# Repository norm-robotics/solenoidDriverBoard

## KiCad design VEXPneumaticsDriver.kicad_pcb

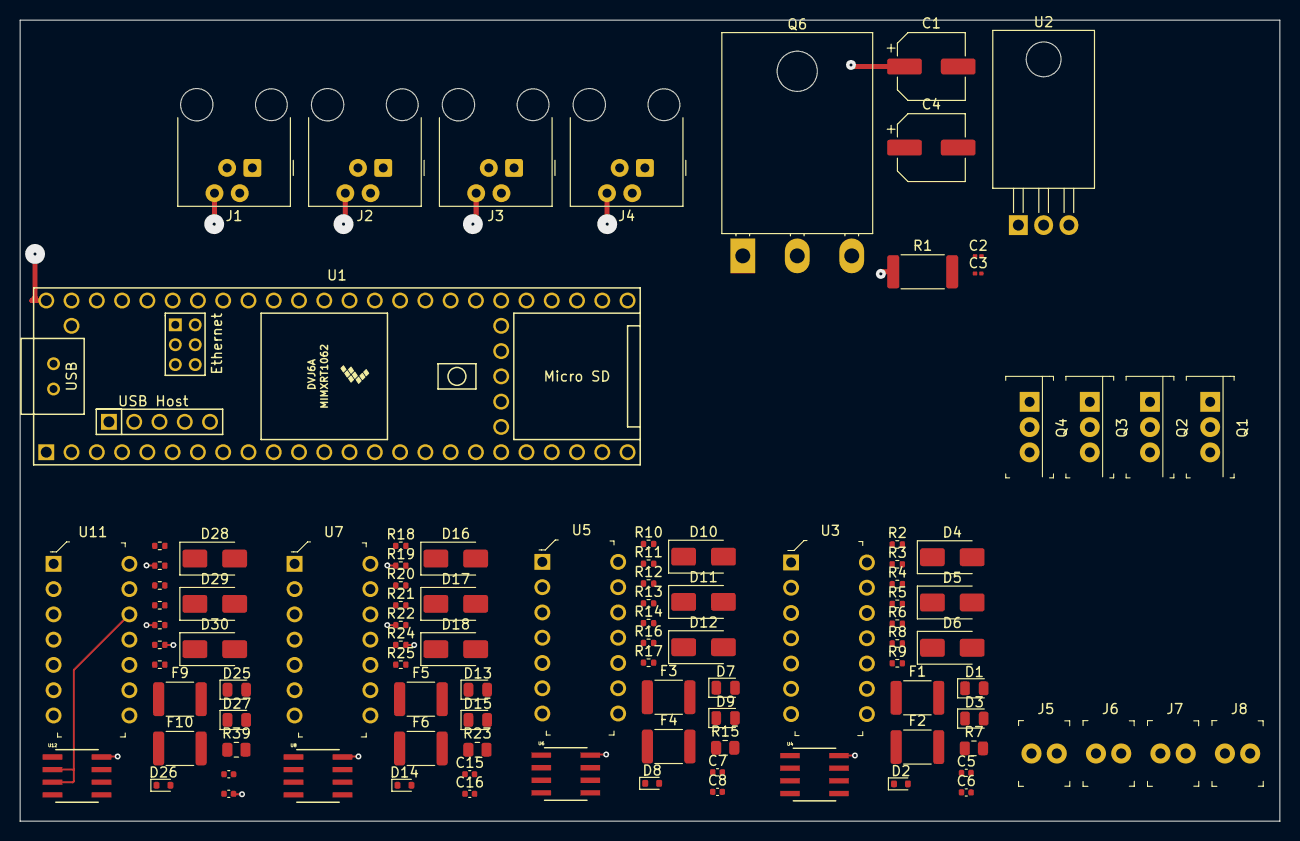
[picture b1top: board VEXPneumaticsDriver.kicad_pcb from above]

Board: 4 copper layers, 126.6 x 80.5 mm, 100 parts (0 on the bottom side), 76 nets.

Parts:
C1: 220uF; CP_Elec_6.3x7.7
C2, C3: 0.1uF; C_0201_0603Metric
C4: 22uF; CP_Elec_6.3x7.7
C5, C7, C9, C15: 100pF; C_0402_1005Metric
C6, C8, C14, C16: 100nF; C_0402_1005Metric
D1, D3, D7, D9, D13, D15, D25, D27: LED; LED_0805_2012Metric
D2, D8, D14, D26: 1N4148WT; D_SOD-523
D4, D5, D6, D10, D11, D12, D16, D17, D18, D28, D29, D30: SMAJ58CA; D_SMA
F1, F2, F3, F4, F5, F6, F9, F10: Fuse; Fuse_1812_4532Metric
J1, J2, J3, J4: 4P4C; RJ9_Evercom_5301-440xxx_Horizontal
J5, J6, J7, J8: 22-23-2021; PinHeader_1x2_P2.54mm_Drill1.02mm
Q1, Q2, Q3, Q4: TIP120; TO-220-3
Q6: TIP2955; TO-218-3_Horizontal_TabDown
R1: 3.3; R_2512_6332Metric
R2, R5, R10, R13, R18, R21, R34, R37: 470; R_0402_1005Metric
R3, R6, R8, R9, R11, R14, R16, R17, R19, R22, R24, R25, R35, R38, R40, R41: 4.7K; R_0402_1005Metric
R4, R12, R20, R36: 56K; R_0402_1005Metric
R7, R15, R23, R39: 120; R_0805_2012Metric
U1: Teensy4.1; Teensy41
U2: LM7805_TO220; TO-220-3_Horizontal_TabDown
U3, U5, U7, U11: SN74HC14N; DIP-14_W3mm
U4, U6, U8, U12: MAX485CSA; 21-0041B_8

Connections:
/12V to 5V Converter/5V: C3.1, C4.1, C6.2, C8.2, C14.2, C16.2, Q6.2 (C), R3.1, R6.1, R8.2, R11.1, R14.1, R16.2, R19.1, R22.1, R24.2, R35.1, R38.1, R40.2, U1.48 (VIN), U2.3 (VO), U3.14 (VCC), U4.8 (VCC), U5.14 (VCC), U6.8 (VCC), U7.14 (VCC), U8.8 (VCC), U11.14 (VCC), U12.8 (VCC)
/12V to 5V Converter/12V: C1.1, J1.4, J2.4, J3.4, J4.4, Q1.2 (C), Q2.2 (C), Q3.2 (C), Q4.2 (C), Q6.3 (E), R1.1
/12V to 5V Converter/IGND: C1.2, C2.2, C3.2, C4.2, C5.2, C6.1, C7.2, C8.1, C9.2, C14.1, C15.2, C16.1, D1.1 (K), D3.1 (K), D7.1 (K), D9.1 (K), D13.1 (K), D15.1 (K), D25.1 (K), D27.1 (K), J5.2, J6.2, J7.2, J8.2, R9.2, R17.2, R25.2, R41.2, U1.47 (GND), U2.2 (GND), U3.7 (GND), U4.5 (GND), U5.7 (GND), U6.5 (GND), U7.7 (GND), U8.5 (GND), U11.7 (GND), U12.5 (GND)
/RS485 to TTL Converter1/A: F2.1, J2.1, R7.2
/RS485 to TTL Converter1/B: F1.1, J2.2, R7.1
/RS485 to TTL Converter1/COM: D4.2 (A2), D6.1 (A1), J2.3
/RS485 to TTL Converter1/RX: U1.9 (7_RX2_OUT1A), U3.4 (2Y), U3.5 (3A)
/RS485 to TTL Converter1/TX: R3.2, U1.10 (8_TX2_IN1), U3.1 (1A)
/RS485 to TTL Converter2/A: F4.1, J3.1, R15.2
/RS485 to TTL Converter2/B: F3.1, J3.2, R15.1
/RS485 to TTL Converter2/COM: D10.2 (A2), D12.1 (A1), J3.3
/RS485 to TTL Converter2/RX: U1.17 (25_A11_RX6_SDA2), U5.4 (2Y), U5.5 (3A)
/RS485 to TTL Converter2/TX: R11.2, U1.16 (24_A10_TX6_SCL2), U5.1 (1A)
/RS485 to TTL Converter3/A: F6.1, J4.1, R23.2
/RS485 to TTL Converter3/B: F5.1, J4.2, R23.1
/RS485 to TTL Converter3/COM: D16.2 (A2), D18.1 (A1), J4.3
/RS485 to TTL Converter3/RX: U1.20 (28_RX7), U7.4 (2Y), U7.5 (3A)
/RS485 to TTL Converter3/TX: R19.2, U1.21 (29_TX7), U7.1 (1A)
/RS485 to TTL Converter/A: F10.1, J1.1, R39.2
/RS485 to TTL Converter/B: F9.1, J1.2, R39.1
/RS485 to TTL Converter/COM: D28.2 (A2), D30.1 (A1), J1.3
/RS485 to TTL Converter/RX: U1.2 (0_RX1_CRX2_CS1), U11.4 (2Y), U11.5 (3A)
/RS485 to TTL Converter/TX: R35.2, U1.3 (1_TX1_CTX2_MISO1), U11.1 (1A)
unnamed: D1.2 (A), R2.2
unnamed: C5.1, D2.2 (A), R4.1, U3.13 (6A)
unnamed: D2.1 (K), R4.2, U3.10 (5Y), U4.4 (DI)
unnamed: D3.2 (A), R5.2
unnamed: D4.1 (A1), D5.2 (A2), F1.2, R9.1, U4.7 (B)
unnamed: D5.1 (A1), D6.2 (A2), F2.2, R8.1, U4.6 (A)
unnamed: D7.2 (A), R10.2
unnamed: C7.1, D8.2 (A), R12.1, U5.13 (6A)
unnamed: D8.1 (K), R12.2, U5.10 (5Y), U6.4 (DI)
unnamed: D9.2 (A), R13.2
unnamed: D10.1 (A1), D11.2 (A2), F3.2, R17.1, U6.7 (B)
unnamed: D11.1 (A1), D12.2 (A2), F4.2, R16.1, U6.6 (A)
unnamed: D13.2 (A), R18.2
unnamed: C15.1, D14.2 (A), R20.1, U7.13 (6A)
unnamed: D14.1 (K), R20.2, U7.10 (5Y), U8.4 (DI)
unnamed: D15.2 (A), R21.2
unnamed: D16.1 (A1), D17.2 (A2), F5.2, R25.1, U8.7 (B)
unnamed: D17.1 (A1), D18.2 (A2), F6.2, R24.1, U8.6 (A)
unnamed: D25.2 (A), R34.2
unnamed: C9.1, D26.2 (A), R36.1, U11.13 (6A)
unnamed: D26.1 (K), R36.2, U11.10 (5Y), U12.4 (DI)
unnamed: D27.2 (A), R37.2
unnamed: D28.1 (A1), D29.2 (A2), F9.2, R41.1, U12.7 (B)
unnamed: D29.1 (A1), D30.2 (A2), F10.2, R40.1, U12.6 (A)
unnamed: Q1.1 (B), U1.7 (5_IN2)
unnamed: J8.1, Q1.3 (E)
unnamed: Q2.1 (B), U1.6 (4_BCLK2)
unnamed: J7.1, Q2.3 (E)
unnamed: Q3.1 (B), U1.5 (3_LRCLK2)
unnamed: J6.1, Q3.3 (E)
unnamed: Q4.1 (B), U1.4 (2_OUT2)
unnamed: J5.1, Q4.3 (E)
unnamed: C2.1, Q6.1 (B), R1.2, U2.1 (VI)
unnamed: R2.1, U3.2 (1Y), U3.11 (5A)
unnamed: U3.3 (2A), U3.8 (4Y)
unnamed: R5.1, U3.6 (3Y)
unnamed: R6.2, U3.9 (4A), U4.1 (RO)
unnamed: U3.12 (6Y), U4.2 (*RE), U4.3 (DE)
unnamed: R10.1, U5.2 (1Y), U5.11 (5A)
unnamed: U5.3 (2A), U5.8 (4Y)
unnamed: R13.1, U5.6 (3Y)
unnamed: R14.2, U5.9 (4A), U6.1 (RO)
unnamed: U5.12 (6Y), U6.2 (*RE), U6.3 (DE)
unnamed: R18.1, U7.2 (1Y), U7.11 (5A)
unnamed: U7.3 (2A), U7.8 (4Y)
unnamed: R21.1, U7.6 (3Y)
unnamed: R22.2, U7.9 (4A), U8.1 (RO)
unnamed: U7.12 (6Y), U8.2 (*RE), U8.3 (DE)
unnamed: R34.1, U11.2 (1Y), U11.11 (5A)
unnamed: U11.3 (2A), U11.8 (4Y)
unnamed: R37.1, U11.6 (3Y)
unnamed: R38.2, U11.9 (4A), U12.1 (RO)
unnamed: U11.12 (6Y), U12.2 (*RE), U12.3 (DE)
